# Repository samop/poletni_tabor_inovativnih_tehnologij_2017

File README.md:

Geiger counter
==============

Geiger counter with Si3-BG Geiger tube. It is very insensitive and it  requires 400V to operate. With some modifications in hardware it can be adapted for use with other (more sensitive) tubes.

Schematics (Hardware)
---------------------

In schematics you can find the source in KiCAD. The circuit consists is a simple buck converter with NE555 that increases voltage from 5V to approx. 400V. I suggest using 555 chip from Texas instruments. The rest is simple 2x16 lcd display module pinout, power supply with switch and pin configuration for codecting nodeMCU module with ESP8266.

There are many ways on how to improve the basic circuit ;).

Software installation instructions
----------------------------------

1. To upload micropython run 'flash.sh'. The esp8266 board should be connected as ttyUSB0, otherwise change the script.
2. To upload geiger-muller counter firmware run 'uploadfw.sh ssid_name channel_number'. (again, be sure board is connected as ttyUSB0.
3. Reset and enjoy

if you want to autostart firmware add line
put main.py into mpfshellscript

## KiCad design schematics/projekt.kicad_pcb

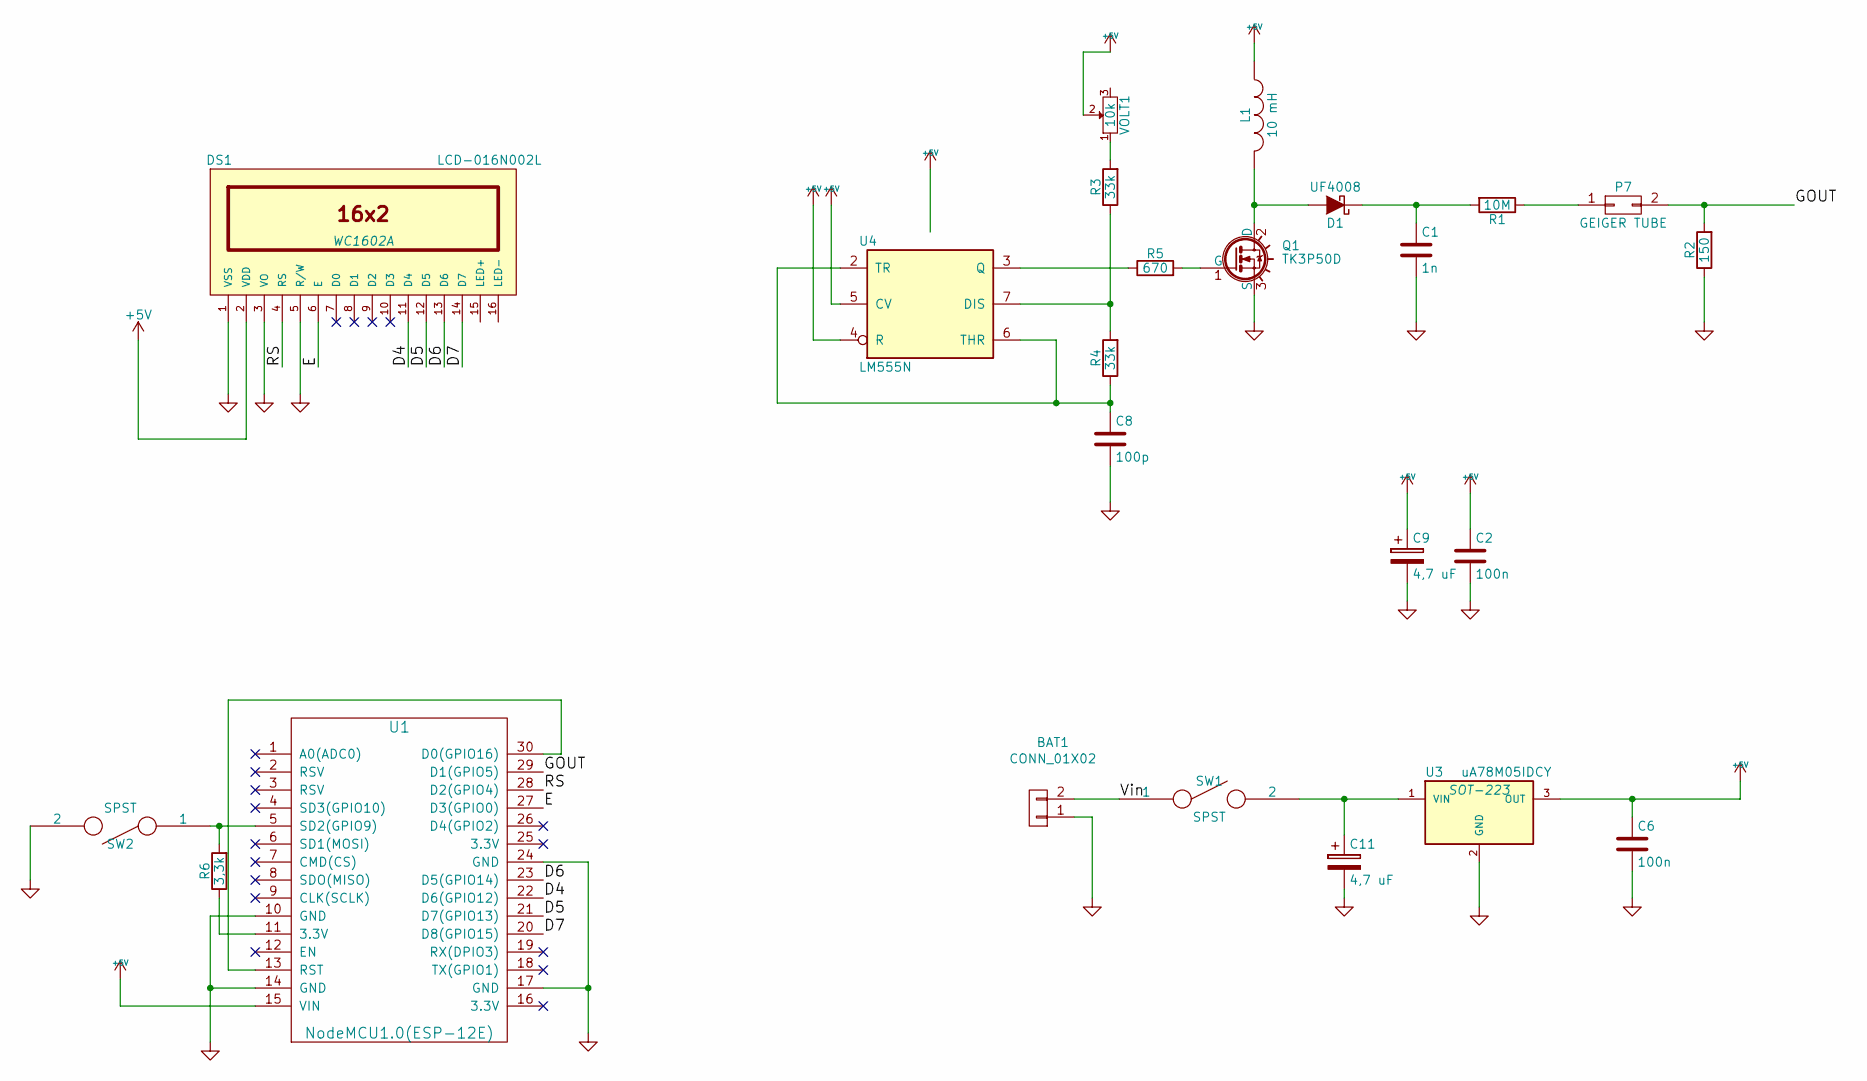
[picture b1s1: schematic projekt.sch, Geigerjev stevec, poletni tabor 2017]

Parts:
BAT1: CONN_01X02; Pin_Header_Straight_1x02_Pitch3.96mm_Friction_Lock
C1: 1n; C_Rect_L7_W2_P5
C2, C6: 100n; C_1206_HandSoldering
C8: 100p; C_Rect_L7_W2_P5
C9, C11: 4,7 uF; Elko_vert_11.5x8mm_RM3.5
D1: UF4008; Diode_DO-35_SOD27_Horizontal_RM10
DS1: LCD-016N002L; WC1602A
L1: 10 mH; Neosid_Inductor_SM-NE127
P7: GEIGER TUBE; SI3BG
Q1: TK3P50D; TO-220
R1: 10M; Resistor_Horizontal_RM10mm
R2: 150; Resistor_Horizontal_RM10mm
R3, R4: 33k; Resistor_Horizontal_RM10mm
R5: 670; Resistor_Horizontal_RM10mm
R6: 3,3k; Resistor_Horizontal_RM10mm
SW1: SPST; slide_switch
SW2: SPST; Pin_Header_Straight_1x02_Pitch3.96mm_Friction_Lock
U1: NodeMCU1.0(ESP-12E); NodeMCU1.0(12-E)
U3: uA78M05IDCY; SOT-223
U4: LM555N; DIP-8_W7.62mm_LongPads
VOLT1: 10k; Potentiometer_Bourns_3296W_3-8Zoll_Inline_ScrewUp

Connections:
+5V: C2.1, C6.1, C9.1, DS1.2 (VDD), L1.1, U1.15 (VIN), U3.3 (OUT), U4.4 (R), U4.5 (CV), U4.8 (VCC), VOLT1.2
/D4: DS1.11 (D4), U1.22 (D6(GPIO12))
/D5: DS1.12 (D5), U1.21 (D7(GPIO13))
/D6: DS1.13 (D6), U1.23 (D5(GPIO14))
/D7: DS1.14 (D7), U1.20 (D8(GPIO15))
/E: DS1.6 (E), U1.27 (D3(GPIO0))
/GOUT: P7.2, R2.2, U1.29 (D1(GPIO5))
/RS: DS1.4 (RS), U1.28 (D2(GPIO4))
/Vin: BAT1.2, SW1.1
GND: BAT1.1, C1.2, C2.2, C6.2, C8.2, C9.2, C11.2, DS1.1 (VSS), DS1.3 (VO), DS1.5 (R/W), Q1.3 (S), R2.1, SW2.2, U1.10 (GND), U1.14 (GND), U1.17 (GND), U1.24 (GND), U3.2 (GND), U4.1 (GND)
unnamed: C1.1, D1.1 (K), R1.2
unnamed: C8.1, R4.1, U4.2 (TR), U4.6 (THR)
unnamed: C11.1, SW1.2, U3.1 (VIN)
unnamed: D1.2 (A), L1.2, Q1.2 (D)
unnamed: P7.1, R1.1
unnamed: Q1.1 (G), R5.2
unnamed: R3.1, R4.2, U4.7 (DIS)
unnamed: R3.2, VOLT1.1
unnamed: R5.1, U4.3 (Q)
unnamed: R6.1, U1.11 (3.3V)
unnamed: R6.2, SW2.1, U1.5 (SD2(GPIO9))
unnamed: U1.13 (RST), U1.30 (D0(GPIO16))

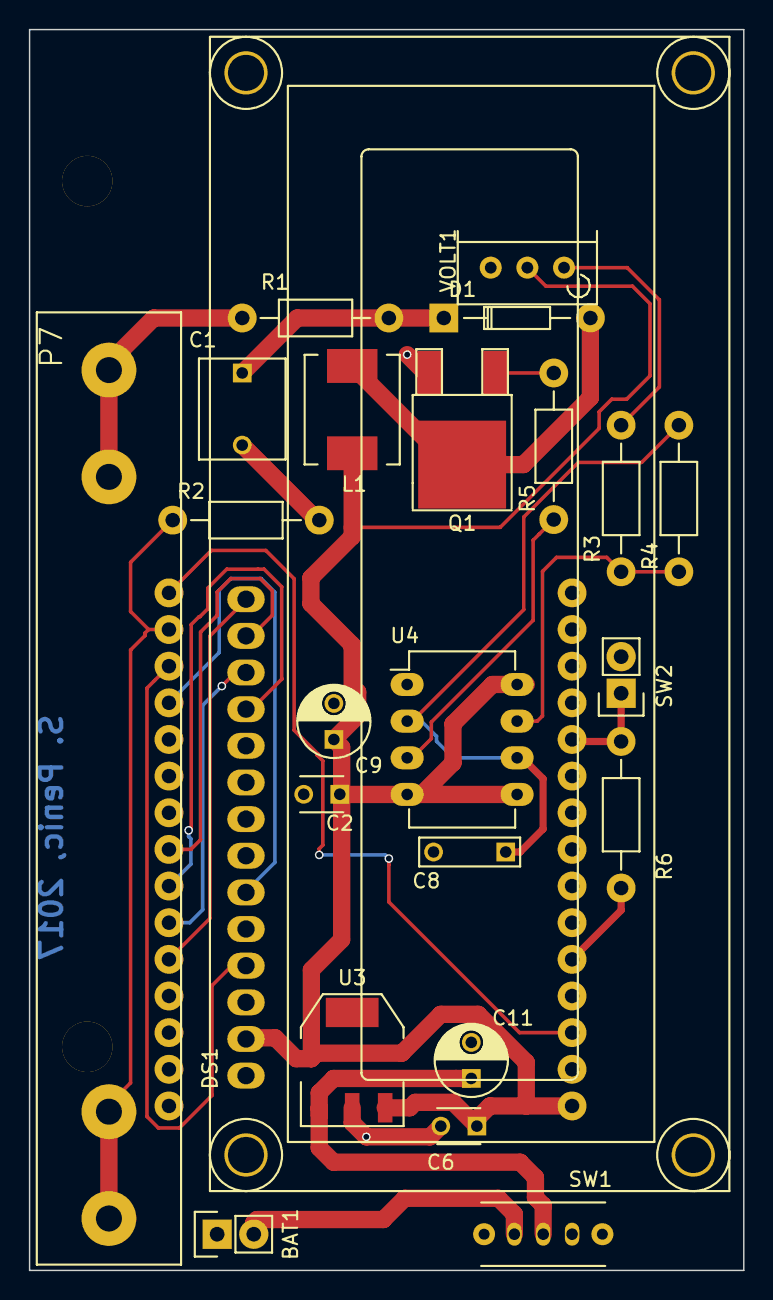
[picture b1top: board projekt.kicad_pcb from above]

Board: 2 copper layers, 49.5 x 86.0 mm, 24 parts (1 on the bottom side), 22 nets.

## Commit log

2017-09-28 Added schematics
